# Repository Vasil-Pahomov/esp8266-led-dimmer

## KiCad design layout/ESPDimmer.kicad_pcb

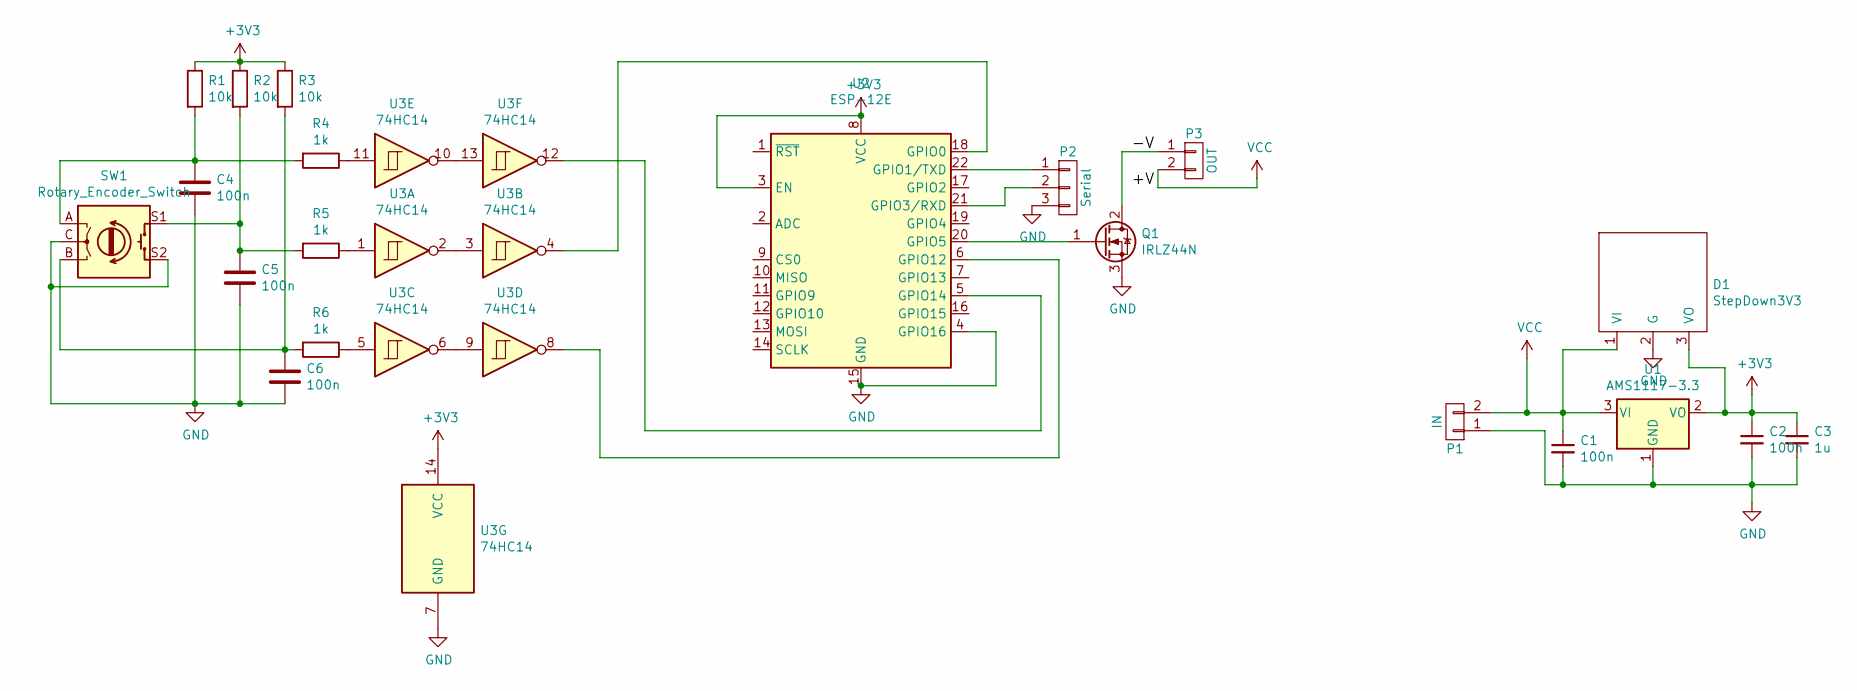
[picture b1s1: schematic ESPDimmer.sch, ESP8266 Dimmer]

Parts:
C1, C2, C4, C5, C6: 100n; C_0805_2012Metric_Pad1.18x1.45mm_HandSolder
C3: 1u; C_0805_2012Metric_Pad1.18x1.45mm_HandSolder
D1: StepDown3V3; TO-220-3_Vertical
P1: IN; PinHeader_1x02_P2.54mm_Vertical
P2: Serial; PinHeader_1x03_P2.54mm_Vertical
P3: OUT; PinHeader_1x02_P2.54mm_Vertical
Q1: IRLZ44N; TO-220-3_Horizontal_TabDown
R1, R2, R3: 10k; R_0805_2012Metric_Pad1.20x1.40mm_HandSolder
R4, R5, R6: 1k; R_0805_2012Metric_Pad1.20x1.40mm_HandSolder
SW1: Rotary_Encoder_Switch; RotaryEncoder_Alps_EC11E-Switch_Vertical_H20mm_CircularMoun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
U1: AMS1117-3.3; SOT-223-3_TabPin2
U2: ESP-12E; ESP-12E_SMD_CHI
U3: 74HC14; SOIC-14_3.9x8.7mm_P1.27mm

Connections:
+3V3: C2.1, C3.1, D1.3 (VO), R1.1, R2.1, R3.1, U1.2 (VO), U2.3 (EN), U2.8 (VCC), U3.14 (VCC)
/-V: P3.1, Q1.2 (D)
GND: C1.2, C2.2, C3.2, C4.2, C5.2, C6.2, D1.2 (G), P1.1, P2.3, Q1.3 (S), SW1.C, SW1.S2, U1.1 (GND), U2.4 (GPIO16), U2.15 (GND), U3.7 (GND)
unnamed: C4.1, R1.2, R4.2, SW1.A
unnamed: C5.1, R2.2, R5.2, SW1.S1
unnamed: C6.1, R3.2, R6.2, SW1.B
unnamed: P2.1, U2.22 (GPIO1/TXD)
unnamed: P2.2, U2.21 (GPIO3/RXD)
unnamed: Q1.1 (G), U2.20 (GPIO5)
unnamed: R4.1, U3.11
unnamed: R5.1, U3.1
unnamed: R6.1, U3.5
unnamed: U2.5 (GPIO14), U3.12
unnamed: U2.6 (GPIO12), U3.8
unnamed: U2.18 (GPIO0), U3.4
unnamed: U3.2, U3.3
unnamed: U3.6, U3.9
unnamed: U3.10, U3.13
VCC: C1.1, D1.1 (VI), P1.2, P3.2, U1.3 (VI)

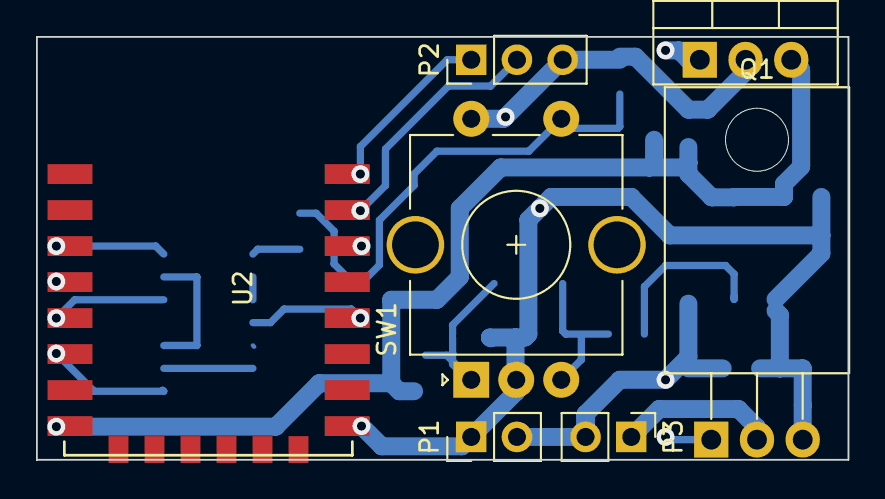
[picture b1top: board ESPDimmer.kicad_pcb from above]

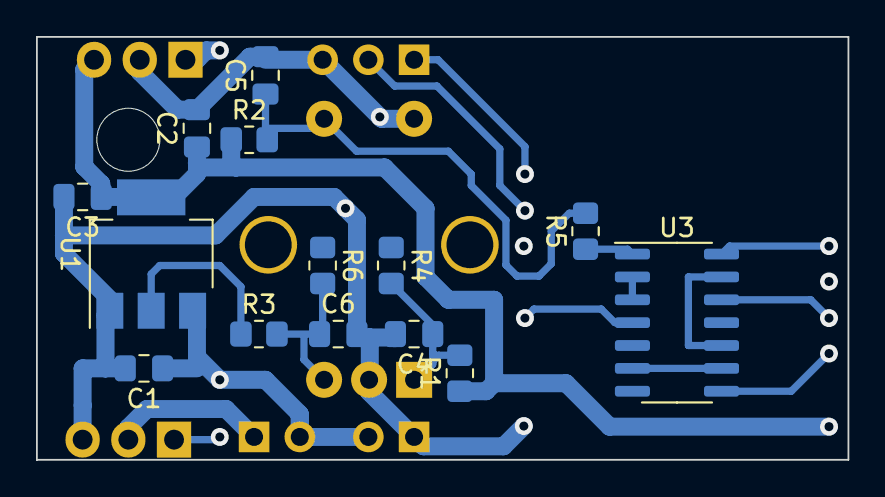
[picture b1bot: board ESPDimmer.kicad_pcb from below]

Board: 2 copper layers, 45.1 x 23.5 mm, 21 parts (14 on the bottom side), 19 nets.

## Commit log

2022-04-16 Updated schematic and PCB, initial firmware (no wifi, only encoder control)
2022-10-08 Added NTP and basic web UI
2022-11-13 Fade in/out works for turning on and off
